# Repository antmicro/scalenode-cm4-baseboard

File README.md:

# Scalenode CM4 Baseboard

Copyright (c) 2020-2023 [Antmicro](https://www.antmicro.com)

## Overview

This project contains the PCB design files for a baseboard supporting System on Modules with pinout compatible with Raspberry Pi Compute Module 4 (CM4).
The baseboard has been optimized for 19-inch rack mount installations for distributed multi-node computing systems.

## Project structure

The main directory contains KiCad PCB project files, a [LICENSE](LICENSE), and a README.
The remaining files are stored in the following directories:

* `lib` - contains the KiCad component libraries
* `doc` - contains generated schematics and other documentation
* `img` - contains graphics for this README
* `assets` - contains visual assets for showcasing this design on [Open Hardware Portal](https://openhardware.antmicro.com)

## Key features

* Supports Raspberry Pi CM4
* Gigabit Ethernet with integrated PoE circuitry
* On-board M.2 (key-M) slot supporting NVMe SSDs 
* Slim PCB outline for 1U chassis
* Expansion connector for peripherals connected over USB
* Expansion connector for HDMI adapters

## Block diagram

## License

This project is published under the [Apache-2.0](LICENSE) license.

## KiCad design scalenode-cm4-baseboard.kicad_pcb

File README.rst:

=======================
Scalenode CM4 Baseboard
=======================

Copyright (c) 2020-2021 `Antmicro <https://www.antmicro.com>`_

.. figure:: img/scalenode.jpg

Overview
========

This repository contains the PCB design files for a baseboard supporting System on Modules with pinout compatible with Raspberry Pi Compute Module 4 (CM4).
The baseboard has been optimized for 19-inch rack mount installations for distributed multi-node computing systems.

Key features
============

* Supports Raspberry Pi CM4
* Gigabit Ethernet with integrated PoE circuitry
* On-board M.2 (key-M) slot supporting NVMe SSDs 
* Slim PCB outline for 1U chassis
* Expansion connector for peripherals connected over USB
* Expansion connector for HDMI adapters

Board layout and dimensions
===========================

.. image:: img/scalenode-dimensions.png

License
=======

`Apache-2.0 <LICENSE>`_

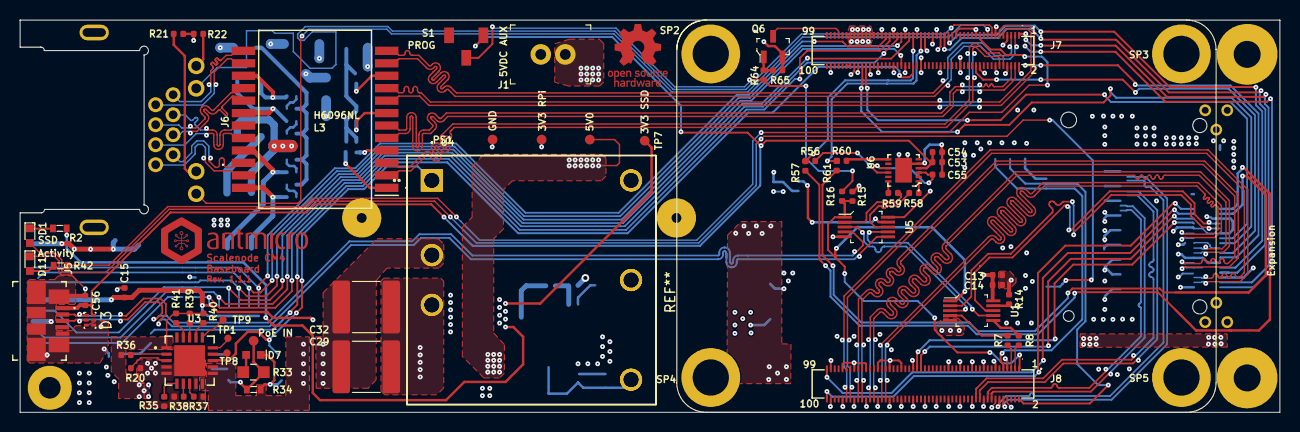
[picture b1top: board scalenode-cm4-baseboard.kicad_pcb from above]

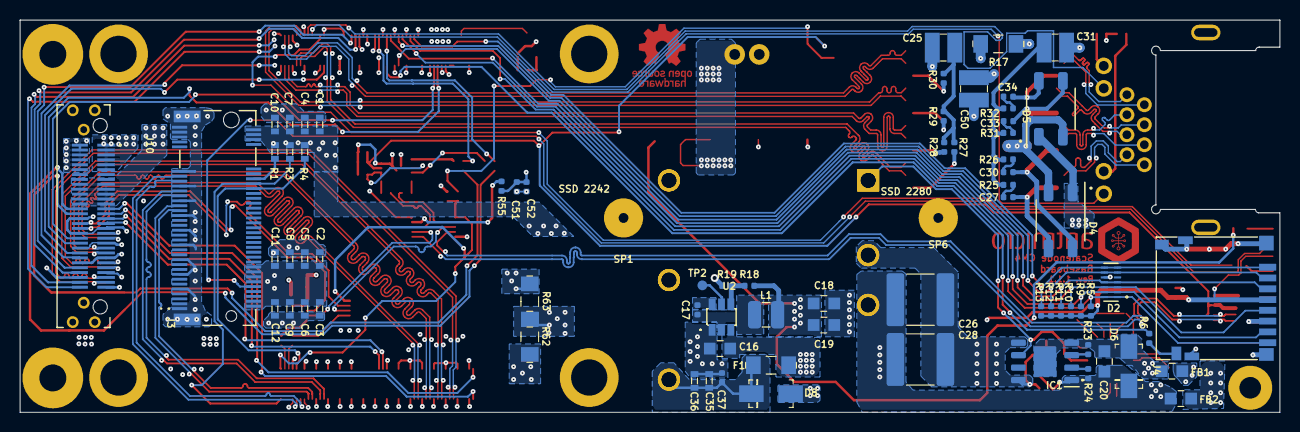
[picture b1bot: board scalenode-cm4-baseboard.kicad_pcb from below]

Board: 4 copper layers, 128.5 x 40.0 mm, 145 parts (74 on the bottom side), 135 nets.

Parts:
C1, C2, C3: C_10u_0603; 0603-cap
C4, C5, C6: C_1u_0603; 0603-cap
C7, C8, C9: C_100n_0603; 0603-cap
C10, C11, C12: C_1n_0603; 0603-cap
C13, C17, C37, C51, C54, C55, C56: C_100n_0402; 0402-cap
C14, C15, C52, C53: C_1u_0402; 0402-cap
C16, C18, C19: C_22u_0805_10V; 0805-cap
C20: C_100n_0805_100V; 0805-cap
C25, C31, C50: C_1n_1210_2kV; 1210-cap
C26, C28, C29, C32: C_22u_2220_100V; 2220-cap
C27, C30, C33, C34: C_10n_0402; 0402-cap
C35, C36: C_47u_0603; 0603-cap
D1, D11: 598-8D80-107F; LED_0603_R
D2: SP3011-06UTG; SON50P350X135X55-14N
D3: TPD4S012DRYR; UFDFN-6_1.45x1mm
D4, D5: SOIC245P670X290-4N; SOIC-4_4.2x5.0mm_P5.7mm
D6: SMAJ58A-13-F; DO-214AC
D7: KP-1608CGCK; LED_0603
D8: SMAJ6.5A; DO-214AC
F1: 1206L450SLWR; 1206-res
FB1, FB2: BLM21PG221SN1D; 0805-res
IC1: TPS2378DDA; SOIC127P600X170-9N
J1: B2B-XH-A_LF__SN_; PinHeader_1x2_P2.5mm_Drill1.1mm
J3: CONN_1-2199230-6; 1-2199230-6
J4: 1140084168; MicroSD_1140084168
J5: 0473460001; USB_Micro_B_Female_0473460001
J6: SS-74800-144
J7, J8: DF40HC(3.0)-100DS-0.4v
J10: LSHM-130-01-L-RH-A-S-K-TR; SAMTEC_LSHM-130-01-XXX-RH-A-S-K-XX
L1: SRP3212A-1R0M; SRP3212
L3: H6096NL; SOIC127P1594X685-24N
MP1: PCB_Mount_Hole_2.2_4.5; mounting-hole-2.2mm
MP2, MP3: PCB_Mount_Hole_2.5_6.2; Mount-hole-M2.5
N1: antmicro_logo; antmicro-logo_scaled_15mm
N3: oshw_logo; oshw-logo
PS1: PDQE30-Q48-S5-D; PDQE30-Q48
Q6: BSS138-7-F; SOT-23-3
R1, R3, R4: R_10k_0603; 0603-res
R2: R_270R_0603; 0603-res
R5, R9, R10, R11, R12, R13, R14, R19, R39, R40, R41, R55, R65: R_10k_0402; 0402-res
R6: R_330R_0402; 0402-res
R7, R8, R58, R59: R_22R_0402; 0402-res
R15: R_2k2_0402; 0402-res
R16: R_1k1_0402; 0402-res
R17, R62, R63: R_0R_1206; 1206-res
R18: R_33k2_0402; 0402-res
R20, R23, R35: R_63R4_0402; 0402-res
R21, R22, R56, R57, R60, R61: R_220R_0402; 0402-res
R24, R36: R_24k9_0402; 0402-res
R25, R26, R27, R28, R29, R30, R31, R32: R_75R_0402; 0402-res
R33: R_32k4_0805; 0805-res
R34: R_15k_0603; 0603-res
R37: R_1k3_0402; 0402-res
R38: R_49k9_0402; 0402-res
R42: R_1k_0603; 0603-res
R64: R_470R_0402; 0402-res
S1: CAS-120TA; Switch_Slide_CAS-120TA
SP1, SP6: 97730256332R
SP2, SP3, SP4, SP5: 9774030151
TP1, TP8, TP9: TP_SMD_0_75MM; Testpoint_smd_0_75mm
TP2, TP3, TP4, TP5, TP6, TP7: TP_SMD1MM; Testpoint_smd_1mm
U1, U5: TS3USB30EDGSR; MSOP-10_W3mm
U2: AP62301WU-7; AP62301WU-7-TSOT23-6
U3: TPS2373-3RGW; QFN65P500X500X100-21N
U4: URB4805YMD-30WR3
U6: FT234XD-R; DFN-12-1EP_3x3mm

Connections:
3V3_OUT: J10.02, J10.04, J10.06, J10.08, J10.10, J10.12, R62.1, R63.1
3V3_RPi: C13.1, C14.1, C15.1, C51.1, C52.1, D11.1, J4.4 (VDD), J7.78, J7.84, J7.86, R5.1, R9.1, R10.1, R11.1, R12.1, R13.1, R21.2, R22.2, R63.2, TP6.1, U1.10 (VCC), U5.10 (VCC)
3V3_SSD: C1.1, C2.1, C3.1, C4.1, C5.1, C6.1, C7.1, C8.1, C9.1, C10.1, C11.1, C12.1, C18.1, C19.1, J3.2 (3V3), J3.4 (3V3), J3.12 (3V3), J3.14 (3V3), J3.16 (3V3), J3.18 (3V3), J3.70 (3V3), J3.72 (3V3), J3.74 (3V3), L1.2, R1.1, R2.2, R3.1, R4.1, R18.2, R62.2, TP7.1
/Compute module/nRPi_BOOT: J7.93, Q6.3 (D)
/Interfaces/CONN_USB_N: D3.1 (D+), J5.2, U5.6 (D-)
/Interfaces/CONN_USB_P: D3.2 (D-), J5.3, U5.4 (D+)
/Interfaces/FTDI_USB_N: R58.1, U5.8 (D1-)
/Interfaces/FTDI_USB_P: R59.1, U5.2 (D1+)
/Interfaces/RPi_USB_N: U1.7 (D2-), U5.7 (D2-)
/Interfaces/RPi_USB_P: U1.3 (D2+), U5.3 (D2+)
/Interfaces/VBus_Slave: C53.1, C54.1, C56.1, D3.6 (VBUS), J5.1, S1.1, U6.4 (VCC)
/PoE/PAIR12: C27.1, D4.3, L3.24 (MCT1)
/PoE/PAIR36: C30.1, D4.4, L3.21 (MCT2)
/PoE/PAIR45: C33.1, D5.3, L3.18 (MCT3)
/PoE/PAIR78: C34.1, D5.4, L3.15 (MCT4)
/PoE/POE_ACTIVE: IC1.6 (CDB), PS1.1 (CTRL), U3.13 (PG), U4.1 (CTRL)
/PoE/T_ETH_D0_N: J6.2, L3.22 (MX1-)
/PoE/T_ETH_D0_P: J6.1, L3.23 (MX1+)
/PoE/T_ETH_D1_N: J6.6, L3.19 (MX2-)
/PoE/T_ETH_D1_P: J6.3, L3.20 (MX2+)
/PoE/T_ETH_D2_N: J6.5, L3.16 (MX3-)
/PoE/T_ETH_D2_P: J6.4, L3.17 (MX3+)
/PoE/T_ETH_D3_N: J6.8, L3.13 (MX4-)
/PoE/T_ETH_D3_P: J6.7, L3.14 (MX4+)
/PoE/VDD_POE_IN: C20.1, C26.1, C28.1, C29.1, C32.1, D6.K, FB2.2, IC1.1 (VDD), PS1.3 (VIN), R24.1, R33.2, R34.2, R36.1, R39.2, R40.2, R41.2, TP3.1, U3.1 (VDD), U4.3 (VIN)
/PoE/VO5V: C35.1, C36.1, C37.1, D8.K, F1.1, PS1.4 (VO), U4.4 (+VO)
Adapter_RXD: J10.28, R57.2
Adapter_TXD: J10.30, R61.1
Adapter_USB_N: J10.34, U1.8 (D1-)
Adapter_USB_P: J10.36, U1.2 (D1+)
ETH_LEDG: J6.11, J7.15
ETH_LEDY: J6.9, J7.17
Earth: C31.2, C50.2, J6.SH, R17.1
GND: C1.2, C2.2, C3.2, C4.2, C5.2, C6.2, C7.2, C8.2, C9.2, C10.2, C11.2, C12.2, C13.2, C14.2, C15.2, C16.2, C18.2, C19.2, C25.1, C35.2, C36.2, C37.2, C50.1, C51.2, C52.2, C53.2, C54.2, C55.2, C56.2, D2.10 (GND), D3.4 (GND), D8.A, J1.2, J3.1 (GND), J3.3 (GND), J3.9 (GND), J3.15 (GND), J3.21 (GND), J3.27 (GND), J3.33 (GND), J3.39 (GND), J3.45 (GND), J3.51 (GND), J3.57 (GND), J3.71 (GND), J3.73 (GND), J3.75 (GND), J3.SH, J4.6 (VSS), J4.10 (CD2), J4.SH (Shell), J5.5, J5.SH, J7.1, J7.2, J7.7, J7.8, J7.13, J7.14, J7.22, J7.23, J7.32, J7.33, J7.42, J7.43, J7.52, J7.53, J7.59, J7.60, J7.65, J7.66, J7.71, J7.74, J7.98, J8.7, J8.8, J8.13, J8.14, J8.19, J8.20, J8.25, J8.26, J8.31, J8.32, J8.37, J8.38, J8.44, J8.50, J8.55, J8.56, J8.61, J8.62, J8.67, J8.68, J8.73, J8.74, J8.79, J8.80, J8.85, J8.86, J8.91, J8.92, J8.97, J8.98, J10.17, J10.18, J10.19, J10.20, J10.21, J10.22, J10.23, J10.24, J10.25, J10.26, J10.32, J10.35, J10.38, J10.41, J10.44, J10.47, J10.50, J10.53, J10.56, J10.59, J10.S1 (SHIELD), J10.S2 (SHIELD), PS1.6 (0V), Q6.2 (S), R14.2, R15.1, R17.2, R19.1, R55.2, R65.2, TP4.1, U1.5 (GND), U2.1 (GND), U4.6 (0V), U5.5 (GND), U6.5 (GND), U6.13 (GND)
GNDD: C26.2, C28.2, C29.2, C32.2, D7.2, IC1.5 (RTN), IC1.8 (APD), PS1.2 (GND), R34.1, U3.10 (APD), U3.11 (RTNA), U3.12 (RTNB), U4.2 (GND)
GPIO3: J7.56, R6.1
GPIO7: J7.37, J10.52
GPIO8: J7.39, J10.54
GPIO18: J7.49, J10.48
GPIO24: J7.45, J10.58
GPIO25: J7.41, J10.60
GPIO26: J7.24, J10.46
HDMI0_CEC: J8.51, J10.31
HDMI0_CK_N: J8.90, J10.57
HDMI0_CK_P: J8.88, J10.55
HDMI0_D0_N: J8.84, J10.51
HDMI0_D0_P: J8.82, J10.49
HDMI0_D1_N: J8.78, J10.45
HDMI0_D1_P: J8.76, J10.43
HDMI0_D2_N: J8.72, J10.39
HDMI0_D2_P: J8.70, J10.37
HDMI0_HOTPLUG: J8.53, J10.33
HDMI0_SCL: J8.100, J10.27
HDMI0_SDA: J8.99, J10.29
unnamed: C17.1, U2.6 (BST)
unnamed: C17.2, L1.1, U2.2 (SW)
unnamed: C25.2, R27.1, R28.1, R29.1, R30.1
unnamed: C27.2, R25.1
unnamed: C30.2, R26.1
unnamed: C31.1, R25.2, R26.2, R31.2, R32.2
unnamed: C33.2, R31.1
unnamed: C34.2, R32.1
unnamed: C55.1, U6.2 (RESET#), U6.3 (3.3VOUT), U6.9 (VCCIO)
unnamed: D1.1, R2.1
unnamed: D1.2, J3.10 (LED)
unnamed: D4.1, D5.1, FB2.1
unnamed: D4.2, D5.2, FB1.1
unnamed: D7.1, R33.1
unnamed: D11.2, R42.2
unnamed: IC1.2 (DEN), R24.2
unnamed: IC1.3 (CLS), R23.1
unnamed: J4.9 (CD1), R6.2
unnamed: J6.10, R21.1
unnamed: J6.12, R22.1
unnamed: J7.21, R42.1
unnamed: L3.1 (TCT1), R27.2
unnamed: L3.4 (TCT2), R28.2
unnamed: L3.7 (TCT3), R29.2
unnamed: L3.10 (TCT4), R30.2
unnamed: Q6.1 (G), R64.2, R65.1
unnamed: R7.2, U1.4 (D+)
unnamed: R8.2, U1.6 (D-)
unnamed: R14.1, U1.9 (~OE)
unnamed: R18.1, R19.2, U2.4 (FB)
unnamed: R20.1, U3.3 (CLSA)
unnamed: R35.1, U3.6 (CLSB)
unnamed: R36.2, U3.2 (DEN)
unnamed: R37.2, U3.8 (AMPS_CTL)
unnamed: R38.2, U3.7 (REF)
unnamed: R39.1, U3.18 (TPH)
unnamed: R40.1, U3.17 (TPL)
unnamed: R41.1, U3.19 (/BT)
unnamed: R55.1, U5.9 (~OE)
unnamed: R56.2, U6.10 (RXD)
unnamed: R58.2, U6.1 (USBDM)
unnamed: R59.2, U6.12 (USBDP)
unnamed: R60.1, U6.7 (TXD)
unnamed: TP1.1, U3.15 (VC_IN)
unnamed: TP2.1, U2.5 (EN)
unnamed: TP8.1, U3.14 (VC_OUT)
unnamed: TP9.1, U3.16 (UVLO_SEL)
PCIE_CLK_N: J3.53 (REFCLK_N), J8.12
PCIE_CLK_P: J3.55 (REFCLK_P), J8.10
PCIE_CLK_nREQ: J3.52 (CLKREQ#), J8.2, R3.2
PCIE_RX_N: J3.41 (PER0_N), J8.18
PCIE_RX_P: J3.43 (PER0_P), J8.16
PCIE_TX_N: J3.47 (PET0_N), J8.24
PCIE_TX_P: J3.49 (PET0_P), J8.22
PCIE_WAKE: J3.54 (PEWAKE#), R1.2
PROG_MODE: R16.2, R64.1, S1.2
PSCIE_nRST: J3.50 (PERST#), J8.9, R4.2
RPi_RXD: J7.51, R60.2, R61.2
RPi_TXD: J7.55, R56.1, R57.1
SCL0: J7.80, J10.40
SDA0: J7.82, J10.42
SD_CLK: D2.12 (D2+), J4.5 (CLK), J7.57, R10.2
SD_CMD: D2.11 (D2-), J4.3 (CMD), J7.62, R11.2
SD_DAT0: D2.13 (D1-), J4.7 (DAT0), J7.63, R9.2
SD_DAT1: D2.14 (D1+), J4.8 (DAT1), J7.67, R5.2
SD_DAT2: D2.8 (D3-), J4.1 (DAT2), J7.69, R13.2
SD_DAT3: D2.9 (D3+), J4.2 (CD/DAT3), J7.61, R12.2
TRD0_N: J7.10, L3.3 (TD1-)
TRD0_P: J7.12, L3.2 (TD1+)
TRD1_N: J7.6, L3.6 (TD2-)
TRD1_P: J7.4, L3.5 (TD2+)
TRD2_N: J7.9, L3.9 (TD3-)
TRD2_P: J7.11, L3.8 (TD3+)
TRD3_N: J7.5, L3.12 (TD4-)
TRD3_P: J7.3, L3.11 (TD4+)
USB2_N: J8.3, R8.1
USB2_P: J8.5, R7.1
USBOTG_ID: J8.1, R15.2, R16.1, U1.1 (S), U5.1 (S)
VCC1V8: J7.88, J7.90
VCC5V0: C16.1, F1.2, J1.1, J7.77, J7.79, J7.81, J7.83, J7.85, J7.87, J10.01, J10.03, J10.05, J10.07, J10.09, J10.11, TP5.1, U2.3 (VIN)
VSS: C20.2, D6.A, FB1.2, IC1.4 (VSS), IC1.9 (EP), R20.2, R23.2, R35.2, R37.1, R38.1, U3.4 (VSSA), U3.5 (VSSB), U3.9 (MPS_DUTY), U3.21 (PAD_VSSC)

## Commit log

2021-02-23 Add LICENSE
2021-02-23 Add rev.1.0.0 design files
2021-02-23 Generate local libraries
2021-02-23 Added 3D visualisation and dimensions drawing
2021-02-23 Add README
2021-02-23 Update header
2021-02-23 Update pcb file
2021-02-23 Review readme
2021-02-23 Added bottom view to dimensions image
2021-02-23 Add PE in PoE coupling
2021-02-23 Add schematic + BOM for rev.1.0.0
2021-02-23 Update designators
2021-02-23 Fix J7 J8 footprints
2021-02-23 Fix logotype
2021-02-23 1.0.0 PCB prototyping
2021-02-24 Added white background to README images
2021-03-29 Added Earthsymbol to lib
2021-03-30 Connect GPIO_VREF signal to 3.3V_RPi
2021-05-01 README: Add photo
2021-08-17 README: Update image property
2022-08-12 README: Update naming
2022-08-12 README: minor fix
2022-08-12 Exchanged flyback to CUI DCDC converter on schematics. Added logos.
2022-08-12 Migration to KiCad 6
2022-08-12 Added text fields with schematic descriptions
2022-08-12 Implemented changes from rev 1.0.4. New components initial placement
2022-08-12 Shortened board. Adjusted posiitons of components. Routed all signals. Added stitching cap
2022-08-12 Optimized routes. Added missing 3D models
2022-08-12 Initial connection of all nets
2022-08-12 Fixed and tuned differential pairs
2022-08-12 Corrected footprints. Adjusted position of testpoints. Cleared DRC
2022-08-12 Added stackup table and defined stackup in board settings
2023-04-04 Add render config
2023-04-04 Loclib
2023-04-04 Update dates in license
2023-04-04 Rename project files
2023-04-04 Fixed silkscreen
2023-04-04 Added alternative PoE chip
2023-04-04 Replaced 3.3V inductor with a smaller one to make m.2 fit
2023-04-04 Corrected R33. Increased distance between L1 and L2. loclib
2023-04-04 Fix license link in readme
2023-04-04 Add badge
2023-04-04 Update readme and change it to MD
2023-04-04 Added comment on MP2162 option
2023-04-04 Bump revision to 1.1.1
2023-04-04 Changed 3V3 converter to AP62301WU-7
2023-04-04 Adjust logo, PCB name and rev to accomodate new project name
2023-04-04 Add URB4805YMD-30WR3 as DNP smps
2023-04-04 Update PCB with DNP smps URB4805YMD-30WR3, review violations
2023-04-04 Update PCB with corrected DF40HC(3.0)-100DS-0.4v footprint
2023-04-04 Fix J7 and J8 designators size
2023-04-04 Remove render config
2023-04-04 README: update wording
2023-04-04 Remove redundant graphics
2023-04-12 added block diagram
2023-04-12 linked README to OSP
2023-05-11 Move ssd mounting points
2023-05-11 Move u6,u5 and nearby passive components
2023-05-11 Move ssd socket and filtering capacitors section
2023-05-11 Move expansion adapter connector
2023-05-11 Add Rpi cm4
2023-05-11 Connect and tuned diff pairs
2023-05-11 Connect gpio
2023-05-11 Move J10 0.8mm left
2023-05-11 Tune difff pairs and Realocate zones
2023-05-11 Connect zones
2023-05-11 Guide tracks out of vias
2023-05-11 Move U5 to create more space for HDMI routing
2023-05-11 Reroute high speed signals and GPIO signals
2023-05-11 Tune high speed signals
2023-05-11 Tune ftdi_usb signal
2023-05-11 Add gnd plane next to PCIe vias
2023-05-11 Connect 3V3OUT planes
2023-05-11 Add stitching capacitors to high speed traces
2023-05-11 Wip after 2nd review
2023-05-11 Reroute PCIe traces and GND connections to expansion connector
2023-05-11 Remove obsolete file
2023-05-11 Add 3V3_SSD zone
2023-05-11 Exclude DRC courtyard error
2023-05-11 Tune hdmi0 tracks
2023-05-11 Improve hdmi0 tuning
2023-05-11 Tune PCIe tracks
2023-05-11 Relocate zones underneath differential pairs
2023-05-11 Add vias around J10
2023-05-12 Update DF40HC(3.0)-100DS-0.4v symbol
2023-05-12 Update DF40HC(3.0)-100DS-0.4v footprint
2023-05-12 Update AP62301WU-7 symbol and footprint
2023-05-12 Update USB-Micro-B_0473460001 symbol and footprint
2023-05-15 Update DF40HC(3.0)-100DS-0.4v symbol and footprint
2023-05-15 Update USB_Micro_B_Female_0473460001 symbol and footprint
2023-05-15 Update TPD4S012DRYR symbol and footprint
2023-05-15 Update TS3USB30EDGSR symbol and footprint
2023-05-15 Update SP3011-06UTG symbol and footprint
2023-05-15 Update MicroSD_1140084168 symbol and footprint
2023-05-15 Update FT234XD-R symbol and footprint
2023-05-15 Update SS-74800-144 symbol and footprint
2023-05-15 Update H6096NL symbol and footprint
2023-05-15 Update MB10S symbol and footprint
2023-05-15 Improved PCB design after 3rd review 15.5.23
2023-05-16 Update PDQE30-Q48-S5-D symbol and footprint
2023-05-16 Update URB4805YMD-30WR3 symbol and footprint
2023-05-16 Update TPS2373-3RGW symbol and QFN65P500X500X100-21N footprint
2023-05-16 Update 1-2199230-6 symbol and footprint
2023-05-16 Tune hdmi0 and PCIe
2023-05-16 Update LSHM-130-01-L-RH-A-S-K-TR symbol and footprint
2023-05-16 Update TPS2378DDA symbol and SOIC127P600X170-9N footprint
2023-05-16 Update C1,C2,C3 symbol and footprint
2023-05-16 Update C4 C5 C6 symbol and footprint
2023-05-16 Update C7 C8 C9 symbol and footprint
2023-05-16 Update C10 C11 C12 symbols and footprints
2023-05-16 Update C13, C17, C21, C37, C51, C54, C55, C56 symbol and footprint
2023-05-16 Update C16, C18, C19 symbol and footprint
2023-05-16 Update C_100n_0805_100V symbol and footprint
2023-05-16 Update C25, C31, C50 symbol and footprint
2023-05-16 Update C26, C28, C29, C32 symbol and footprint
2023-05-16 Update C27, C30, C33, C34 symbol and footprint
2023-05-16 Update C35, C36 symbol and footprint
2023-05-16 Update D1, D11 symbol
2023-05-17 Update D6 symbol and footprint
2023-05-17 Update D7 symbol and footprint
2023-05-17 Update D8 symbol and footprint
2023-05-17 Update F1 symbol and footprint
2023-05-17 Updatae FB1, FB2 symbol and footprint
2023-05-17 Update J1 symbol and footprint
2023-05-17 Update L1 symbol and footprint
2023-05-17 Update M1 symbol and footprint
2023-05-17 Update J1 symbol
2023-05-17 Update FB1 FB2 symbol and footprint
2023-05-17 Update F1 symbol and schematic
2023-05-17 Update L1 symbol
2023-05-17 Update C26, C28, C29, C32 symbol
2023-05-17 Update MP1 symbol and footprint
2023-05-17 Update MP2, MP3 symbol and footprint
2023-05-17 Update N1, N3 symbol and footprint
2023-05-17 Update Q6 symbol and footprint
2023-05-17 Update R1, R3, R4 symbol and footprint
2023-05-17 Update R2 symbol and footprint
2023-05-17 Update R5, R9, R10, R11, R12, R13, R14, R19, R55, R65 symbol and footprint
2023-05-17 Update R6 symbol and footprint
2023-05-17 Update R7, R8, R58, R59 symbol and footprint
2023-05-17 Update R15 symbol and footprint
2023-05-17 Update R16 symbol and footprint
2023-05-17 Update R17, R62, R63 symbol and footprint
2023-05-17 Update R18 symbol and footprint
2023-05-17 Update R21, R22, R56, R57, R60, R61 symbol and footprints
2023-05-17 Update R20 R23 R35 symbol and footprint
2023-05-17 Update R24, R36 symbol and footprint
2023-05-17 Update R25, R26, R27, R28, R29, R30, R31, R32 symbol and footprint
2023-05-17 Update R33 symbol and footprint
2023-05-17 Update R33 footprint
2023-05-17 Update R34 symbol and footprint
2023-05-17 Update R42 symbol and footprint
2023-05-17 Update R64 symbol and footprint
2023-05-18 Update TP1, TP8, TP9 symbol and footprint
2023-05-18 Update R37 symbol and footprint
2023-05-18 Update R38 symbol and footprint
2023-05-18 Update TP2, TP3, TP4, TP5, TP6, TP7 symbol and footprint
2023-05-18 Update S1 symbol and footprint
2023-05-18 Update SP1, SP6 symbol and footprint
2023-05-18 Update SP2, SP3, SP4, SP5 symbol and footprint
2023-05-18 Relocate front and back silkscreen labels
2023-05-18 Updae SOIC127P1594X685-24N footprint
2023-05-19 Remove DRC errors and warnings
2023-05-19 Improve PCIe routing
2023-05-19 Fixed schematic errors
2023-05-19 Update LSHM-130-01-L-RH-A-S-K-TR symbol
2023-05-19 Updated badly connected J10
2023-05-22 Move J10 and reroute HDMI and GPIO tracks
2023-05-22 Tuned hdmi0 and usb tracks
2023-05-22 Move J10 reference
2023-05-23 Reroute USB and tune hdmi0
2023-05-23 Move GND plane
2023-05-23 Cleanup redundant tracks and vias
2023-05-25 Move F.Fab and B.Fab markings from outside the board to the inside
2023-05-25 Validate at PCB Vendor
2023-05-25 Cleanup
2023-05-25 Add PCB SHA string
2023-05-25 Remove redundant project file
2023-06-02 Fix project - "Update PCB from schematic" button works
2023-06-02 Place reference designators on the back
2023-06-02 Place reference designators on the front
2023-06-02 Update C54 and C53 reference
2023-06-07 Update front silk markings
2023-06-07 Update back silk markings
2023-06-12 Set EC 7C technology for DRC
2023-06-12 Fix clearance lower than 0.125mm
2023-06-12 Fix kicad_pro file
2023-06-12 Reduce edge clearance and min hole diameter
2023-06-12 Fix DRC errors
2023-06-12 Increase board length to 128.5mm
2023-06-12 Change gnd track width in expansion connector
2023-06-12 Remove dimensions markings
2023-06-12 Fix DRC warnings
2023-07-18 [#46875] WIP project update
2023-07-19 [#46875] Standardize schematics
2023-07-20 [#46875] Replace Bus_M.2-0.5P-1-2199230-6 symbol
    Replace Bus_M.2-0.5P-1-2199230-6 symbol with Bus_M.2_1-2199230-6
2023-07-20 [#46875] Update DCDC converters' symbols
2023-07-20 [#46875] Add wire between pins 79 and 81 of J7
2023-07-20 [#46875] Remove junction connecting R6 to 3V3_RPi
2023-07-20 [#46875] Update PCB and fix DRC errors
2023-07-20 [#46875] Update schematic symbols
2023-07-20 [#46875] Update PCB after symbol update
2023-07-21 [#46875] Add ERC warnings to exclusions
2023-07-21 [#46875] Update Mount-hole-M2.5
2023-07-21 [#46875] Update PCB with standardized footprints Remove CM4 footprint duplicate
2023-07-21 [#46875] Update DRC exclusions
2023-07-21 [#46875] kmake loclib
2023-07-21 [#46875] Revert kmake loclib
    This reverts commit a23b923226223a7ebbdda1690aa69773ccaf4a95.
2023-07-21 [#46875] Update AP62301WU-7 symbol
2023-07-21 [#46875] Update BSS138-7-F symbol
2023-07-21 [#46875] Update mounting hole symbol
2023-07-21 [#46875] Update TS3USB30EDGSR & TPD4S012DRYR symbols
2023-07-21 [#46875] Update exclusions
2023-07-21 [#46875] Update U6 footprint
2023-07-24 [#46875] Update Spacer_H3mm_9774030151 footprint
2023-07-24 [#46875] Update SS-74800-144 symbol and footprint
2023-07-24 [#46875] Update footprints
2023-07-24 [#46875] Update block diagram
2023-07-24 [#46875] Update PCB
2023-07-24 [#46875] Bump revision to 1.1.2
2023-07-25 Set U3 to DNP
2023-07-25 Place M1 label inside PCB. Hide MP labels
2023-07-25 Update placement of U1 label
2023-07-25 Move U3 DNP to middle of symbol
2023-07-27 Update /doc
2023-07-27 Add /img
2023-07-27 Rename IC1 to U8
2023-07-27 Update ERC exclusions
2023-07-27 Repo cleanup
2023-08-07 Notes added by 'git notes add'
2023-08-10 Change SSD connector symbol to Bus_M.2_MDT580M01001
2023-08-10 Move C28 and C26, switch SSD connector footprint to Bus_M.2_MDT580M01001
2023-08-10 Move SSD 2280 stub
2023-08-10 Change SP1, SP6 to Spacer_H0.5mm_97730406332R
2023-08-11 Fix SP1 and SP6 symbol values
2023-08-11 Move SP6 0.5mm closer to the connector
2023-08-31 [#47798] Added M2 3D model to M2 connector
2023-08-31 Update SP1, SP6 footprints
2023-08-31 [#47798] Corrected CM4 3D model position in z axis
2023-08-31 [#47798] Corrected M2 module 3D model position in z axis
2023-08-31 [#47798] Fix designators on the silkscreen layer
2023-09-12 Update CM4 standoffs to standardized version
    Run loclib
2023-11-06 Remove hidden 3D model from board
2023-11-06 Add OHP assets
2023-11-06 README: mention assets
2023-11-07 Update assets
2024-04-02 [#56969] Correct component references

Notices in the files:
parts and their libraries:
Copyright: Copyright (c) 2023 Antmicro
